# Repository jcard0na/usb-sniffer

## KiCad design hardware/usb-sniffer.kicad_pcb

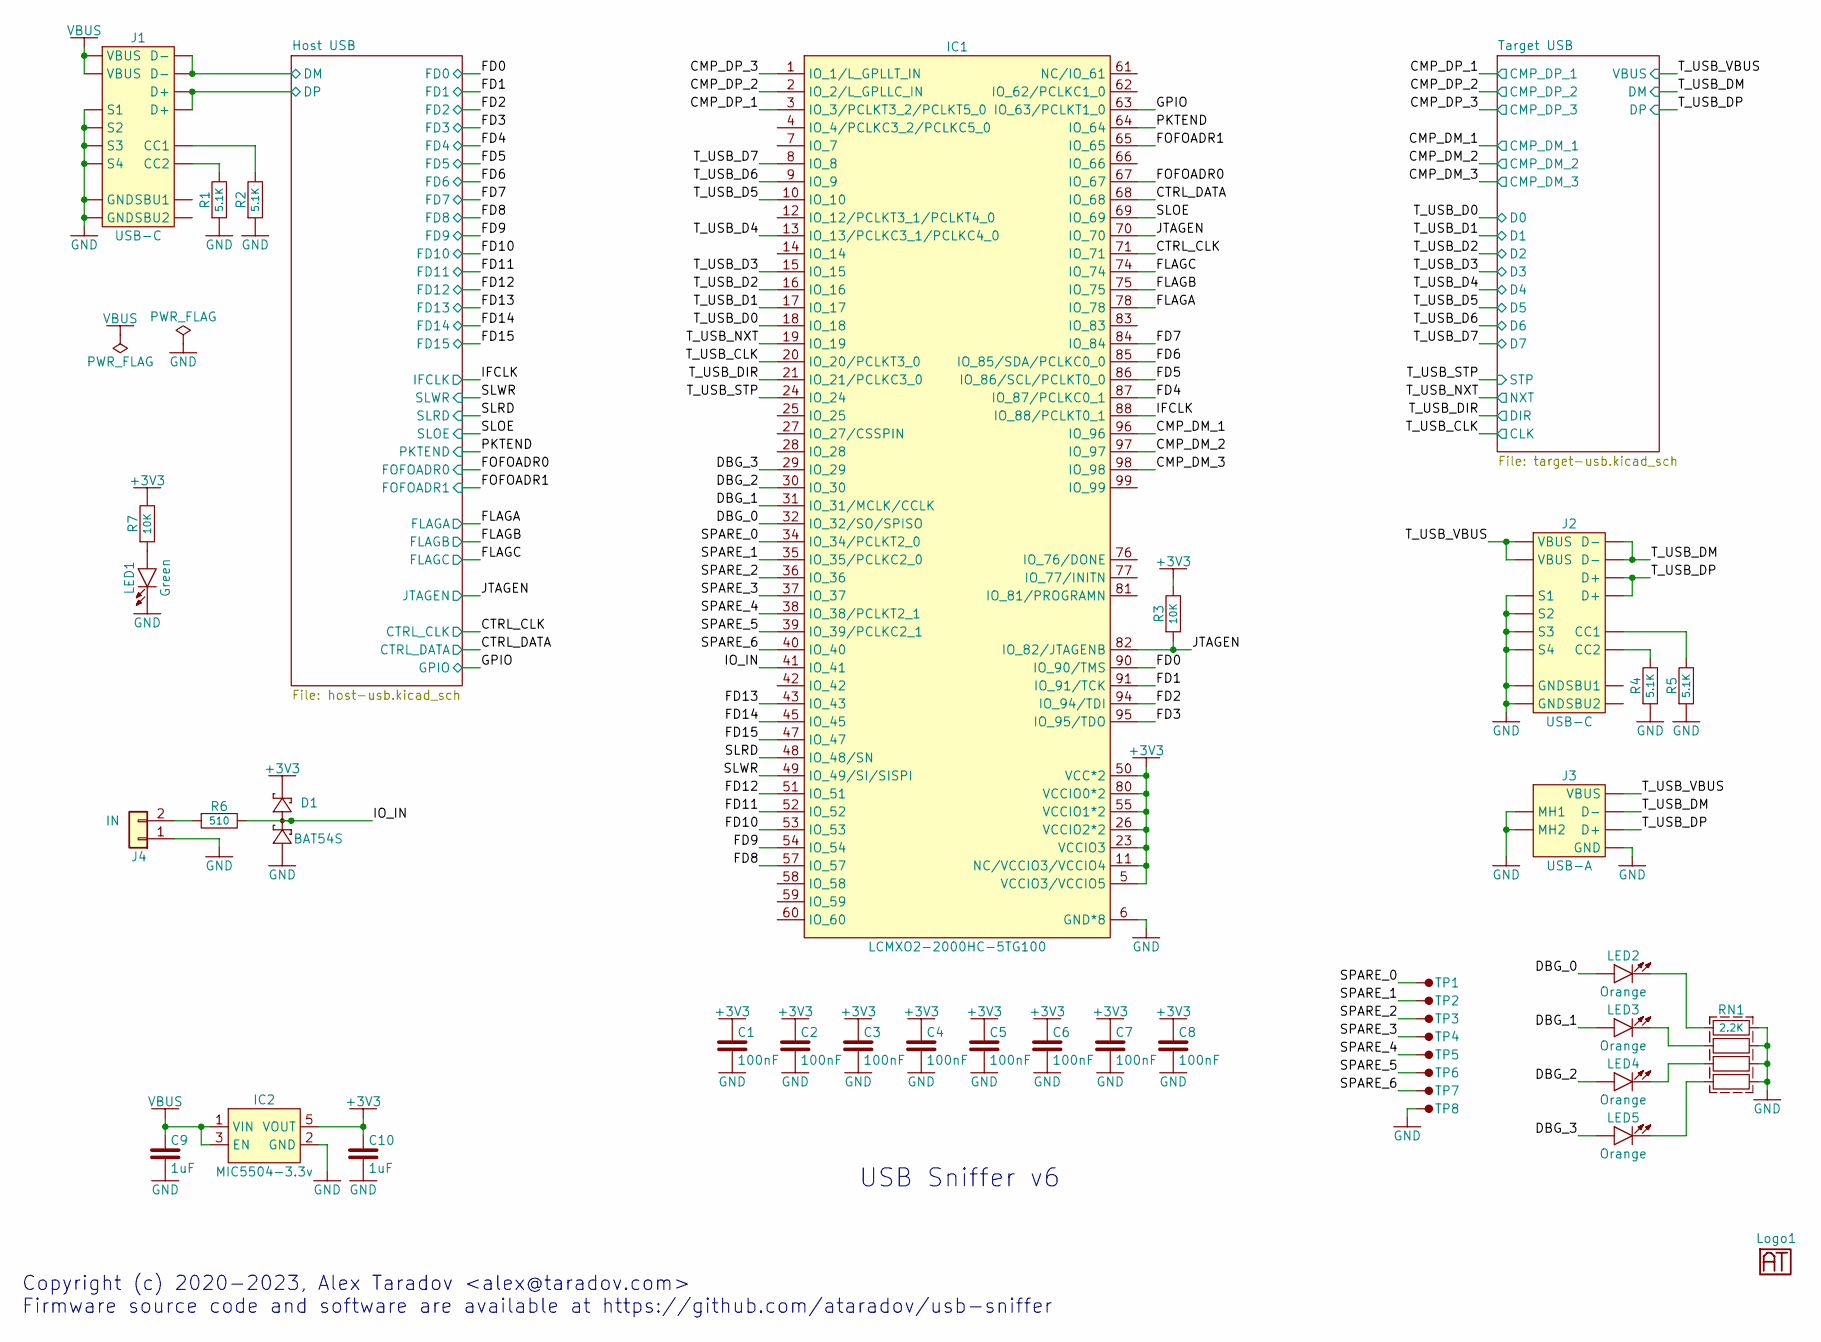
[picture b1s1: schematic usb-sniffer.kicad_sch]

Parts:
C1, C2, C3, C4, C5, C6, C7, C8: 100nF; 0603; LCSC C14663
C9, C10: 1uF; 0603; LCSC C15849
D1: BAT54S; SOT-23; LCSC C47546
IC1: LCMXO2-2000HC-5TG100; TQFP-100-0.5mm
IC2: MIC5504-3.3v; SOT-23-5; LCSC C88419
J1, J2: USB-C; LCSC C2835315
J3: USB-A; C668591; LCSC C668591
J4: IN; PinHeader_1x02_P2.54mm_Horizontal; LCSC C492410
LED1: Green; LED_0603_1608Metric; LCSC C84264
LED2, LED3, LED4, LED5: Orange; LED_0603_1608Metric; LCSC C84269
Logo1: Logo; Logo-Small
R1, R2, R4, R5: 5.1K; 0603; LCSC C23186
R3, R7: 10K; 0603; LCSC C25804
R6: 510; 0603; LCSC C23193
RN1: 2.2K; 0603x4; LCSC C414564
TP1, TP2, TP3, TP4, TP5, TP6, TP7, TP8: TestPoint-1.27mm-Small

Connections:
+3V3: C1.2, C2.2, C3.2, C4.2, C5.2, C6.2, C7.2, C8.2, C10.2, D1.2, IC1.5 (VCCIO3/VCCIO5), IC1.11 (NC/VCCIO3/VCCIO4), IC1.23 (VCCIO3), IC1.26 (VCCIO2*2), IC1.46 (VCCIO2), IC1.50 (VCC*2), IC1.55 (VCCIO1*2), IC1.73 (VCCIO1), IC1.80 (VCCIO0*2), IC1.93 (VCCIO0), IC1.100 (VCC), IC2.5 (VOUT), R3.2, R7.2; also elsewhere on the board
/CMP_DM_1: IC1.96 (IO_96); also elsewhere on the board
/CMP_DM_2: IC1.97 (IO_97); also elsewhere on the board
/CMP_DM_3: IC1.98 (IO_98); also elsewhere on the board
/CMP_DP_1: IC1.3 (IO_3/PCLKT3_2/PCLKT5_0); also elsewhere on the board
/CMP_DP_2: IC1.2 (IO_2/L_GPLLC_IN); also elsewhere on the board
/CMP_DP_3: IC1.1 (IO_1/L_GPLLT_IN); also elsewhere on the board
/CTRL_CLK: IC1.71 (IO_71); also elsewhere on the board
/CTRL_DATA: IC1.68 (IO_68); also elsewhere on the board
/DBG_0: IC1.32 (IO_32/SO/SPISO), LED2.1 (A)
/DBG_1: IC1.31 (IO_31/MCLK/CCLK), LED3.1 (A)
/DBG_2: IC1.30 (IO_30), LED4.1 (A)
/DBG_3: IC1.29 (IO_29), LED5.1 (A)
/FD0: IC1.90 (IO_90/TMS); also elsewhere on the board
/FD1: IC1.91 (IO_91/TCK); also elsewhere on the board
/FD2: IC1.94 (IO_94/TDI); also elsewhere on the board
/FD3: IC1.95 (IO_95/TDO); also elsewhere on the board
/FD4: IC1.87 (IO_87/PCLKC0_1); also elsewhere on the board
/FD5: IC1.86 (IO_86/SCL/PCLKT0_0); also elsewhere on the board
/FD6: IC1.85 (IO_85/SDA/PCLKC0_0); also elsewhere on the board
/FD7: IC1.84 (IO_84); also elsewhere on the board
/FD8: IC1.57 (IO_57); also elsewhere on the board
/FD9: IC1.54 (IO_54); also elsewhere on the board
/FD10: IC1.53 (IO_53); also elsewhere on the board
/FD11: IC1.52 (IO_52); also elsewhere on the board
/FD12: IC1.51 (IO_51); also elsewhere on the board
/FD13: IC1.43 (IO_43); also elsewhere on the board
/FD14: IC1.45 (IO_45); also elsewhere on the board
/FD15: IC1.47 (IO_47); also elsewhere on the board
/FLAGA: IC1.78 (IO_78); also elsewhere on the board
/FLAGB: IC1.75 (IO_75); also elsewhere on the board
/FLAGC: IC1.74 (IO_74); also elsewhere on the board
/FOFOADR0: IC1.67 (IO_67); also elsewhere on the board
/FOFOADR1: IC1.65 (IO_65); also elsewhere on the board
/GPIO: IC1.63 (IO_63/PCLKT1_0); also elsewhere on the board
/Host USB/DM: J1.D-1 (D-), J1.D-2 (D-); also elsewhere on the board
/Host USB/DP: J1.D+1 (D+), J1.D+2 (D+); also elsewhere on the board
/IFCLK: IC1.88 (IO_88/PCLKT0_1); also elsewhere on the board
/IO_IN: D1.3, IC1.41 (IO_41), R6.2
/JTAGEN: IC1.70 (IO_70), IC1.82 (IO_82/JTAGENB), R3.1; also elsewhere on the board
/PKTEND: IC1.64 (IO_64); also elsewhere on the board
/SLOE: IC1.69 (IO_69); also elsewhere on the board
/SLRD: IC1.48 (IO_48/SN); also elsewhere on the board
/SLWR: IC1.49 (IO_49/SI/SISPI); also elsewhere on the board
/SPARE_0: IC1.34 (IO_34/PCLKT2_0), TP1.1
/SPARE_1: IC1.35 (IO_35/PCLKC2_0), TP2.1
/SPARE_2: IC1.36 (IO_36), TP3.1
/SPARE_3: IC1.37 (IO_37), TP4.1
/SPARE_4: IC1.38 (IO_38/PCLKT2_1), TP5.1
/SPARE_5: IC1.39 (IO_39/PCLKC2_1), TP6.1
/SPARE_6: IC1.40 (IO_40), TP7.1
/T_USB_CLK: IC1.20 (IO_20/PCLKT3_0); also elsewhere on the board
/T_USB_D0: IC1.18 (IO_18); also elsewhere on the board
/T_USB_D1: IC1.17 (IO_17); also elsewhere on the board
/T_USB_D2: IC1.16 (IO_16); also elsewhere on the board
/T_USB_D3: IC1.15 (IO_15); also elsewhere on the board
/T_USB_D4: IC1.13 (IO_13/PCLKC3_1/PCLKC4_0); also elsewhere on the board
/T_USB_D5: IC1.10 (IO_10); also elsewhere on the board
/T_USB_D6: IC1.9 (IO_9); also elsewhere on the board
/T_USB_D7: IC1.8 (IO_8); also elsewhere on the board
/T_USB_DIR: IC1.21 (IO_21/PCLKC3_0); also elsewhere on the board
/T_USB_DM: J2.D-1 (D-), J2.D-2 (D-), J3.D-; also elsewhere on the board
/T_USB_DP: J2.D+1 (D+), J2.D+2 (D+), J3.D+; also elsewhere on the board
/T_USB_NXT: IC1.19 (IO_19); also elsewhere on the board
/T_USB_STP: IC1.24 (IO_24); also elsewhere on the board
/T_USB_VBUS: J2.VBUS1 (VBUS), J2.VBUS2 (VBUS), J3.VBUS; also elsewhere on the board
GND: C1.1, C2.1, C3.1, C4.1, C5.1, C6.1, C7.1, C8.1, C9.1, C10.1, D1.1, IC1.6 (GND*8), IC1.22 (GND), IC1.33 (GND), IC1.44 (GND), IC1.56 (GND), IC1.72 (GND), IC1.79 (GND), IC1.92 (GND), IC2.2 (GND), J1.GND1 (GND), J1.GND2 (GND), J1.S1, J1.S2, J1.S3, J1.S4, J2.GND1 (GND), J2.GND2 (GND), J2.S1, J2.S2, J2.S3, J2.S4, J3.GND, J3.MH1, J3.MH2, J4.1, LED1.2 (K), R1.1, R2.1, R4.1, R5.1, RN1.5, RN1.6, RN1.7, RN1.8, TP8.1; also elsewhere on the board
unnamed: J1.CC1, R2.2
unnamed: J1.CC2, R1.2
unnamed: J2.CC1, R5.2
unnamed: J2.CC2, R4.2
unnamed: J4.2, R6.1
unnamed: LED1.1 (A), R7.1
unnamed: LED2.2 (K), RN1.1
unnamed: LED3.2 (K), RN1.2
unnamed: LED4.2 (K), RN1.3
unnamed: LED5.2 (K), RN1.4
VBUS: C9.2, IC2.1 (VIN), IC2.3 (EN), J1.VBUS1 (VBUS), J1.VBUS2 (VBUS)

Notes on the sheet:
Copyright (c) 2020-2023, Alex Taradov <alex@taradov.com> Firmware source code and software are available at https://github.com/ataradov/usb-sniffer
USB Sniffer v6

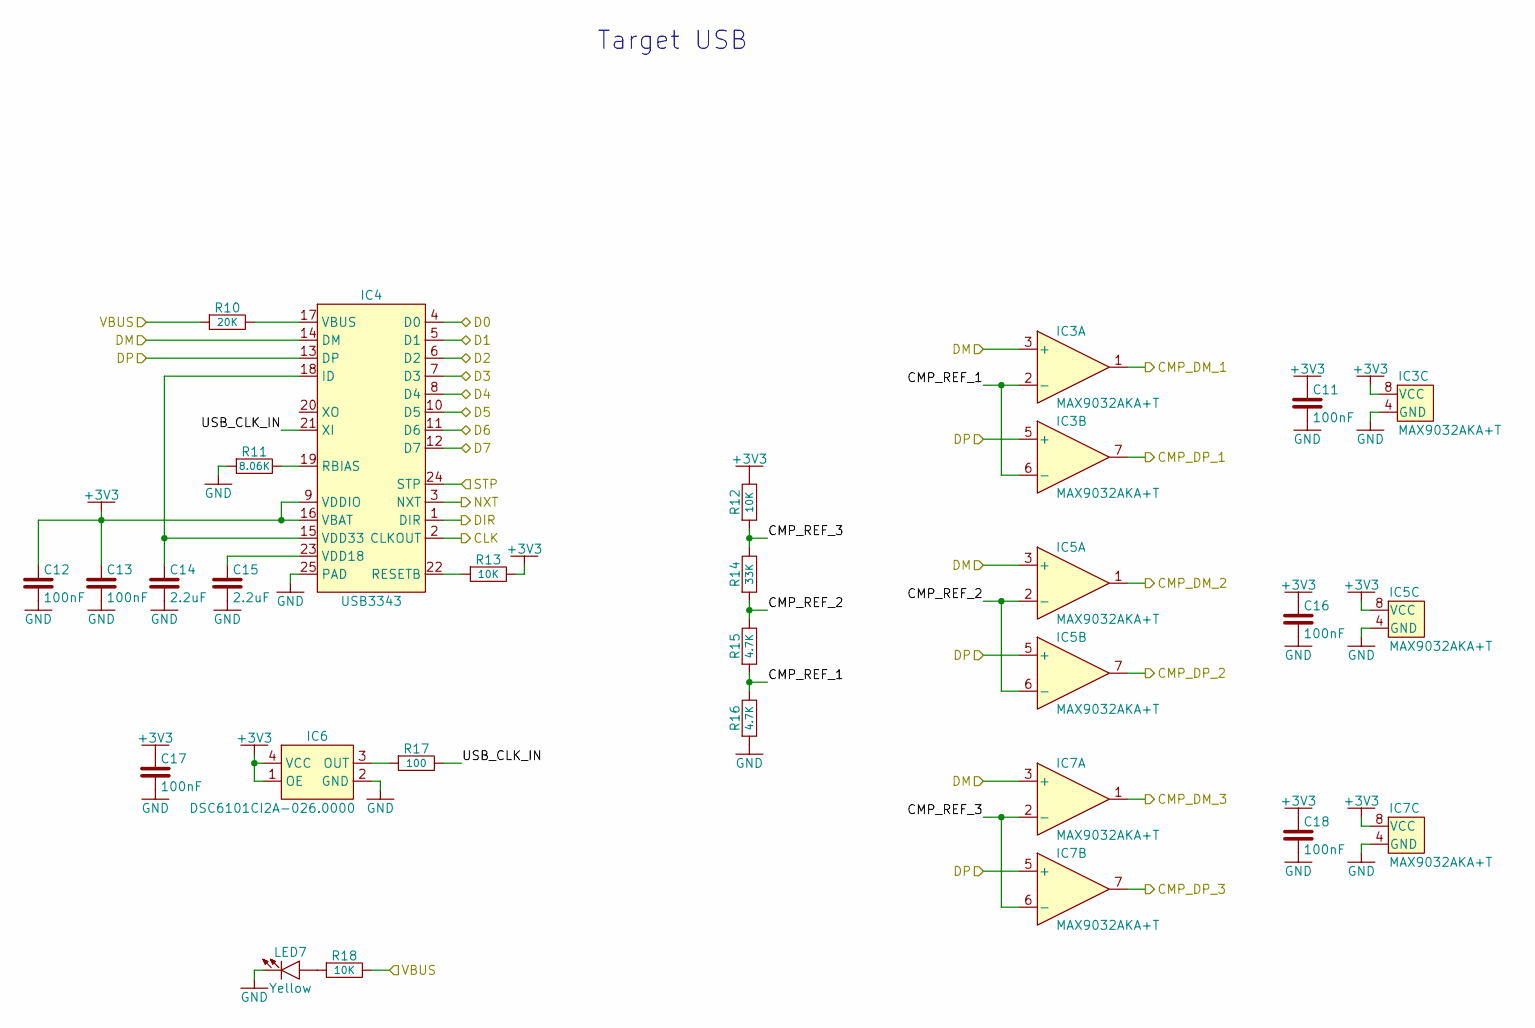
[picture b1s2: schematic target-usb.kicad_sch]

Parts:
C11, C12, C13, C16, C17, C18: 100nF; 0603; LCSC C14663
C14, C15: 2.2uF; 0603; LCSC C23630
IC3, IC5, IC7: MAX9032AKA+T; SOT-23-8; LCSC C571006
IC4: USB3343; QFN-24-0.5mm; LCSC C633347
IC6: DSC6101CI2A-026.0000; CDFN-4-3.2x2.5mm; LCSC C5203550
LED7: Yellow; LED_0603_1608Metric; LCSC C72038
R10: 20K; 0603; LCSC C4184
R11: 8.06K; 0603; LCSC C131052
R12, R13, R18: 10K; 0603; LCSC C25804
R14: 33K; 0603; LCSC C4216
R15, R16: 4.7K; 0603; LCSC C23162
R17: 100; 0603; LCSC C22775

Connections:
+3V3: C11.2, C12.2, C13.2, C16.2, C17.2, C18.2, IC3.8 (VCC), IC4.9 (VDDIO), IC4.16 (VBAT), IC5.8 (VCC), IC6.1 (OE), IC6.4 (VCC), IC7.8 (VCC), R12.2, R13.2; also elsewhere on the board
/CMP_DM_1: IC3.1; also elsewhere on the board
/CMP_DM_2: IC5.1; also elsewhere on the board
/CMP_DM_3: IC7.1; also elsewhere on the board
/CMP_DP_1: IC3.7; also elsewhere on the board
/CMP_DP_2: IC5.7; also elsewhere on the board
/CMP_DP_3: IC7.7; also elsewhere on the board
/T_USB_CLK: IC4.2 (CLKOUT); also elsewhere on the board
/T_USB_D0: IC4.4 (D0); also elsewhere on the board
/T_USB_D1: IC4.5 (D1); also elsewhere on the board
/T_USB_D2: IC4.6 (D2); also elsewhere on the board
/T_USB_D3: IC4.7 (D3); also elsewhere on the board
/T_USB_D4: IC4.8 (D4); also elsewhere on the board
/T_USB_D5: IC4.10 (D5); also elsewhere on the board
/T_USB_D6: IC4.11 (D6); also elsewhere on the board
/T_USB_D7: IC4.12 (D7); also elsewhere on the board
/T_USB_DIR: IC4.1 (DIR); also elsewhere on the board
/T_USB_DM: IC3.3 (+), IC4.14 (DM), IC5.3 (+), IC7.3 (+); also elsewhere on the board
/T_USB_DP: IC3.5 (+), IC4.13 (DP), IC5.5 (+), IC7.5 (+); also elsewhere on the board
/T_USB_NXT: IC4.3 (NXT); also elsewhere on the board
/T_USB_STP: IC4.24 (STP); also elsewhere on the board
/T_USB_VBUS: R10.1, R18.2; also elsewhere on the board
/Target USB/CMP_REF_1: IC3.2 (-), IC3.6 (-), R15.1, R16.2
/Target USB/CMP_REF_2: IC5.2 (-), IC5.6 (-), R14.1, R15.2
/Target USB/CMP_REF_3: IC7.2 (-), IC7.6 (-), R12.1, R14.2
/Target USB/USB_CLK_IN: IC4.21 (XI), R17.2
GND: C11.1, C12.1, C13.1, C14.1, C15.1, C16.1, C17.1, C18.1, IC3.4 (GND), IC4.25 (PAD), IC5.4 (GND), IC6.2 (GND), IC7.4 (GND), LED7.2 (K), R11.1, R16.1; also elsewhere on the board
unnamed: C14.2, IC4.15 (VDD33), IC4.18 (ID)
unnamed: IC4.19 (RBIAS), R11.2
unnamed: IC4.22 (RESETB), R13.1
unnamed: IC4.17 (VBUS), R10.2
unnamed: C15.2, IC4.23 (VDD18)
unnamed: IC6.3 (OUT), R17.1
unnamed: LED7.1 (A), R18.1

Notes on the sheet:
Target USB

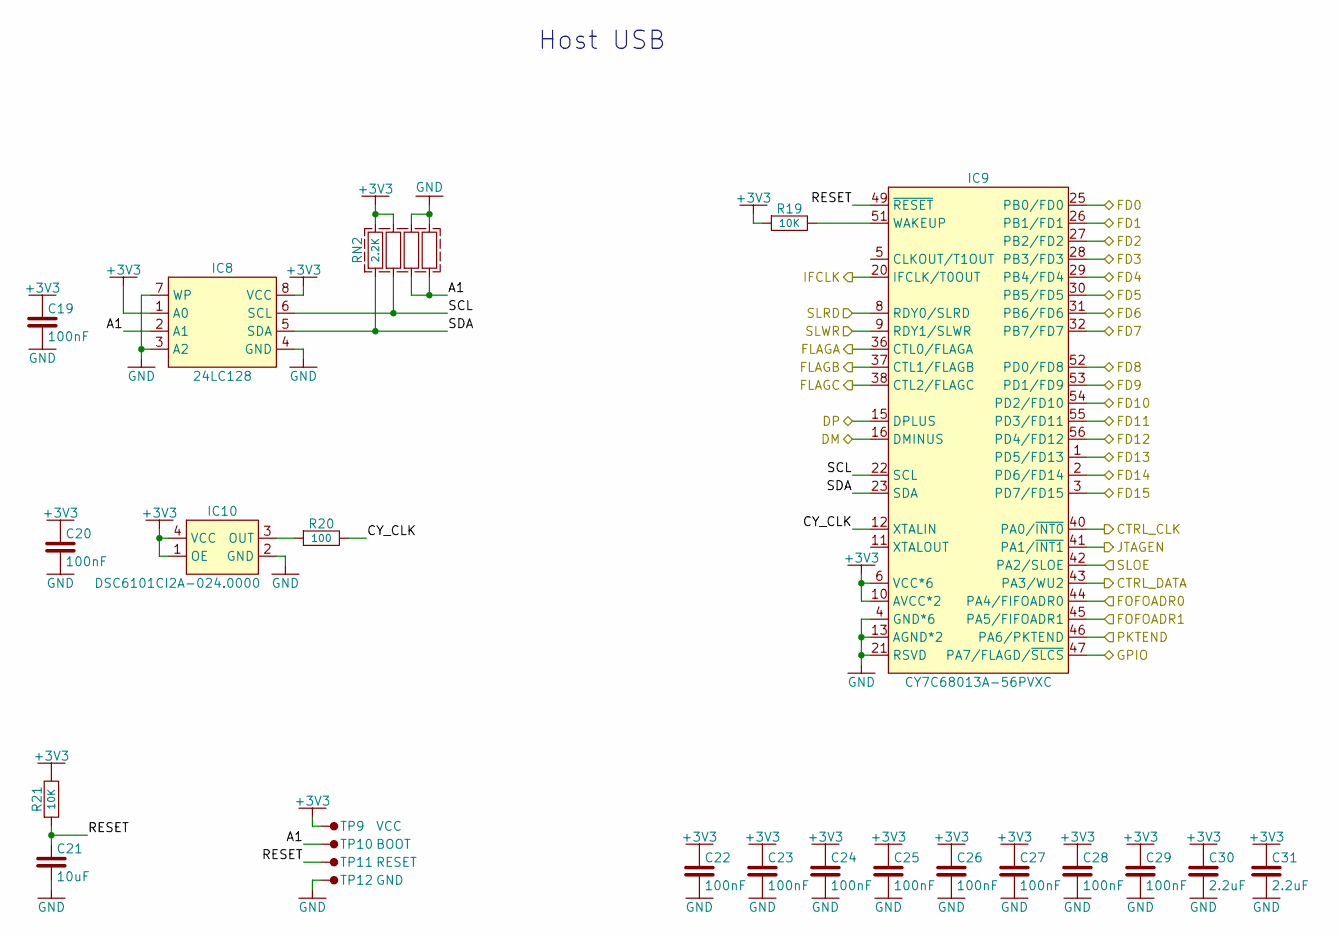
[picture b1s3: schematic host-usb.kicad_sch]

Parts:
C19, C20, C22, C23, C24, C25, C26, C27, C28, C29: 100nF; 0603; LCSC C14663
C21: 10uF; 0603; LCSC C19702
C30, C31: 2.2uF; 0603; LCSC C23630
IC8: 24LC128; SO-8; LCSC C99368
IC9: CY7C68013A-56PVXC; SSOP-56-0.635mm; LCSC C26717
IC10: DSC6101CI2A-024.0000; CDFN-4-3.2x2.5mm; LCSC C5203548
R19, R21: 10K; 0603; LCSC C25804
R20: 100; 0603; LCSC C22775
RN2: 2.2K; 0603x4; LCSC C414564
TP9: VCC; TestPoint-1.27mm
TP10: BOOT; TestPoint-1.27mm
TP11: RESET; TestPoint-1.27mm
TP12: GND; TestPoint-1.27mm

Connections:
+3V3: C19.2, C20.2, C22.2, C23.2, C24.2, C25.2, C26.2, C27.2, C28.2, C29.2, C30.2, C31.2, IC8.1 (A0), IC8.8 (VCC), IC9.6 (VCC*6), IC9.10 (AVCC*2), IC9.14 (AVCC), IC9.18 (VCC), IC9.24 (VCC), IC9.34 (VCC), IC9.39 (VCC), IC9.50 (VCC), IC10.1 (OE), IC10.4 (VCC), R19.1, R21.2, RN2.7, RN2.8, TP9.1; also elsewhere on the board
/CTRL_CLK: IC9.40 (PA0/~INT0); also elsewhere on the board
/CTRL_DATA: IC9.43 (PA3/WU2); also elsewhere on the board
/FD0: IC9.25 (PB0/FD0); also elsewhere on the board
/FD1: IC9.26 (PB1/FD1); also elsewhere on the board
/FD2: IC9.27 (PB2/FD2); also elsewhere on the board
/FD3: IC9.28 (PB3/FD3); also elsewhere on the board
/FD4: IC9.29 (PB4/FD4); also elsewhere on the board
/FD5: IC9.30 (PB5/FD5); also elsewhere on the board
/FD6: IC9.31 (PB6/FD6); also elsewhere on the board
/FD7: IC9.32 (PB7/FD7); also elsewhere on the board
/FD8: IC9.52 (PD0/FD8); also elsewhere on the board
/FD9: IC9.53 (PD1/FD9); also elsewhere on the board
/FD10: IC9.54 (PD2/FD10); also elsewhere on the board
/FD11: IC9.55 (PD3/FD11); also elsewhere on the board
/FD12: IC9.56 (PD4/FD12); also elsewhere on the board
/FD13: IC9.1 (PD5/FD13); also elsewhere on the board
/FD14: IC9.2 (PD6/FD14); also elsewhere on the board
/FD15: IC9.3 (PD7/FD15); also elsewhere on the board
/FLAGA: IC9.36 (CTL0/FLAGA); also elsewhere on the board
/FLAGB: IC9.37 (CTL1/FLAGB); also elsewhere on the board
/FLAGC: IC9.38 (CTL2/FLAGC); also elsewhere on the board
/FOFOADR0: IC9.44 (PA4/FIFOADR0); also elsewhere on the board
/FOFOADR1: IC9.45 (PA5/FIFOADR1); also elsewhere on the board
/GPIO: IC9.47 (PA7/FLAGD/~SLCS); also elsewhere on the board
/Host USB/A1: IC8.2 (A1), RN2.3, RN2.4, TP10.1
/Host USB/CY_CLK: IC9.12 (XTALIN), R20.2
/Host USB/DM: IC9.16 (DMINUS); also elsewhere on the board
/Host USB/DP: IC9.15 (DPLUS); also elsewhere on the board
/Host USB/RESET: C21.2, IC9.49 (~RESET), R21.1, TP11.1
/Host USB/SCL: IC8.6 (SCL), IC9.22 (SCL), RN2.2
/Host USB/SDA: IC8.5 (SDA), IC9.23 (SDA), RN2.1
/IFCLK: IC9.20 (IFCLK/T0OUT); also elsewhere on the board
/JTAGEN: IC9.41 (PA1/~INT1); also elsewhere on the board
/PKTEND: IC9.46 (PA6/PKTEND); also elsewhere on the board
/SLOE: IC9.42 (PA2/SLOE); also elsewhere on the board
/SLRD: IC9.8 (RDY0/SLRD); also elsewhere on the board
/SLWR: IC9.9 (RDY1/SLWR); also elsewhere on the board
GND: C19.1, C20.1, C21.1, C22.1, C23.1, C24.1, C25.1, C26.1, C27.1, C28.1, C29.1, C30.1, C31.1, IC8.3 (A2), IC8.4 (GND), IC8.7 (WP), IC9.4 (GND*6), IC9.7 (GND), IC9.13 (AGND*2), IC9.17 (AGND), IC9.19 (GND), IC9.21 (RSVD), IC9.33 (GND), IC9.35 (GND), IC9.48 (GND), IC10.2 (GND), RN2.5, RN2.6, TP12.1; also elsewhere on the board
unnamed: IC9.51 (WAKEUP), R19.2
unnamed: IC10.3 (OUT), R20.1

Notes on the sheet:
Host USB

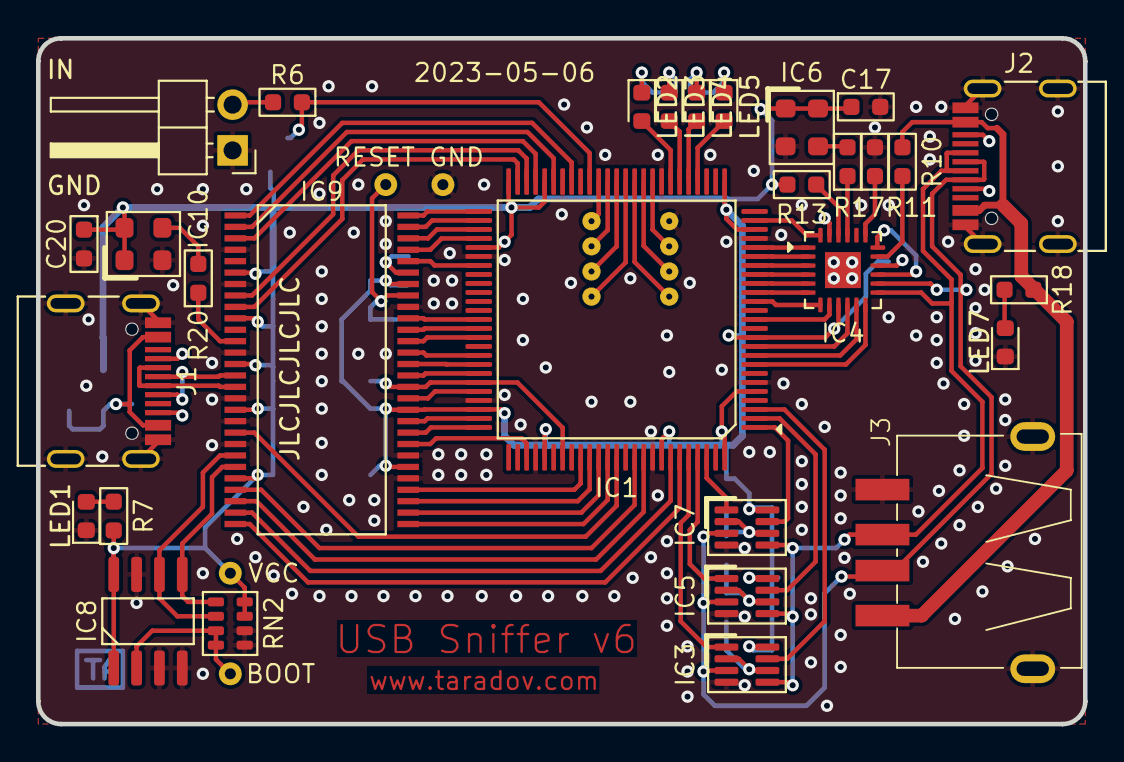
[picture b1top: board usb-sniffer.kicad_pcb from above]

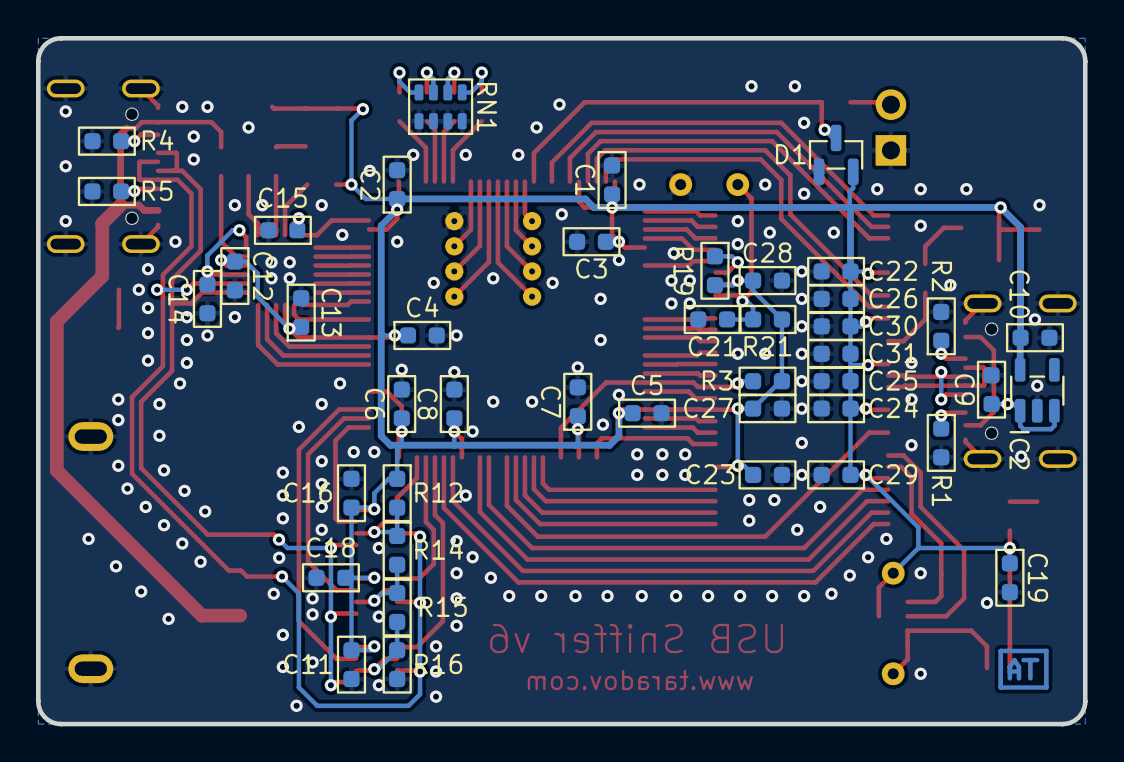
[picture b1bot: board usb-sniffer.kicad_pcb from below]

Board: 2 copper layers, 58.2 x 38.1 mm, 86 parts (44 on the bottom side), 96 nets.

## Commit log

2023-12-19 Select parts for JLCPCB assembly
    Also, modify USB type-A connector for an SMD part that is widely in
    stocked.
2023-12-20 Added some 3d models
2023-12-31 Use LED_SMD:LED_0603_1608Metric footprint for LEDs
